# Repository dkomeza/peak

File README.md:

# peak
A small e-bike display meant for VESC

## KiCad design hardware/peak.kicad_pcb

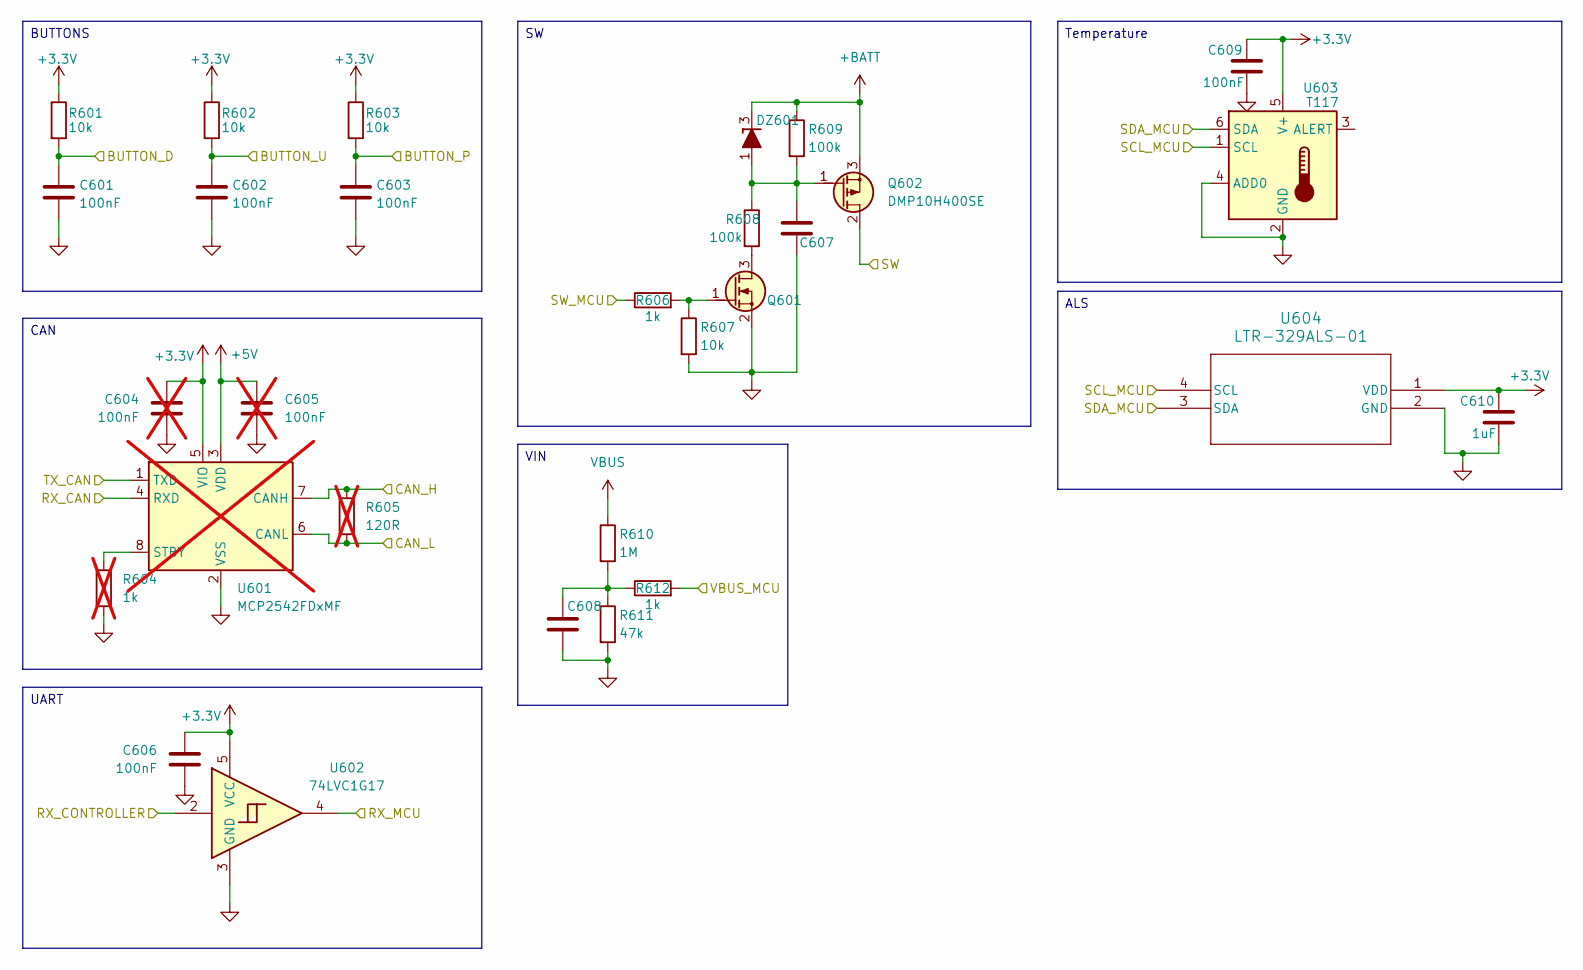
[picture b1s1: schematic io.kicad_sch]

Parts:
C601, C602, C603, C606, C609: 100nF; C_0603_1608Metric
C604, C605: 100nF; C_0603_1608Metric; not fitted
C607: 100nF/100V; C_0805_2012Metric
C608, C610: 1uF; C_0603_1608Metric
DZ601: BZX84-C12; SOT-23
Q601: BSS123; SOT-23
Q602: DMP10H400SE; SOT-223-3_TabPin2
R601, R602, R603, R607: 10k; R_0603_1608Metric
R604: 1k; R_0603_1608Metric; not fitted
R605: 120R; R_0603_1608Metric; not fitted
R606, R612: 1k; R_0603_1608Metric
R608, R609: 100k; R_0805_2012Metric
R610: 1M; R_0603_1608Metric
R611: 47k; R_0603_1608Metric
U601: MCP2542FDxMF; DFN-8-1EP_3x3mm_P0.65mm_EP1.55x2.4mm; not fitted
U602: 74LVC1G17; SOT-23-5
U603: T117; DFN-6-1EP_2x2mm_P0.65mm_EP1x1.6mm
U604: LTR-329ALS-01; LTR-329ALS-01_LTO

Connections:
+3.3V: C604.1, C606.1, C609.1, C610.1, R601.1, R602.1, R603.1, U601.5 (VIO), U602.5 (VCC), U603.5 (V+), U604.1 (VDD); also elsewhere on the board
+5V: C605.1, U601.3 (VDD); also elsewhere on the board
+BATT: DZ601.3 (K), Q602.3 (S), R609.1; also elsewhere on the board
/Connection/Button_D: C601.1, R601.2; also elsewhere on the board
/Connection/Button_P: C603.1, R603.2; also elsewhere on the board
/Connection/Button_U: C602.1, R602.2; also elsewhere on the board
/Connection/CANH: R605.1, U601.7 (CANH); also elsewhere on the board
/Connection/CANL: R605.2, U601.6 (CANL); also elsewhere on the board
/Connection/RX: U602.2; also elsewhere on the board
/Connection/SW: Q602.2 (D); also elsewhere on the board
/IO/SCL_MCU: U603.1 (SCL), U604.4 (SCL); also elsewhere on the board
/IO/SDA_MCU: U603.6 (SDA), U604.3 (SDA); also elsewhere on the board
/IO/SW_MCU: R606.1; also elsewhere on the board
/IO/VBUS_MCU: R612.2; also elsewhere on the board
/MCU/RX1: U601.4 (RXD), U602.4; also elsewhere on the board
/MCU/TX1: U601.1 (TXD); also elsewhere on the board
GND: C601.2, C602.2, C603.2, C604.2, C605.2, C606.2, C607.2, C608.2, C609.2, C610.2, Q601.2 (S), R604.2, R607.2, R611.2, U601.2 (VSS), U601.9 (VSS), U602.3 (GND), U603.2 (GND), U603.4 (ADD0), U604.2 (GND); also elsewhere on the board
unnamed: C608.1, R610.2, R611.1, R612.1
unnamed: C607.1, DZ601.1 (A), Q602.1 (G), R608.1, R609.2
unnamed: Q601.3 (D), R608.2
unnamed: Q601.1 (G), R606.2, R607.1
unnamed: R604.1, U601.8 (STBY)
VBUS: R610.1; also elsewhere on the board

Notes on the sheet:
Temperature
ALS
VIN
UART
BUTTONS
CAN

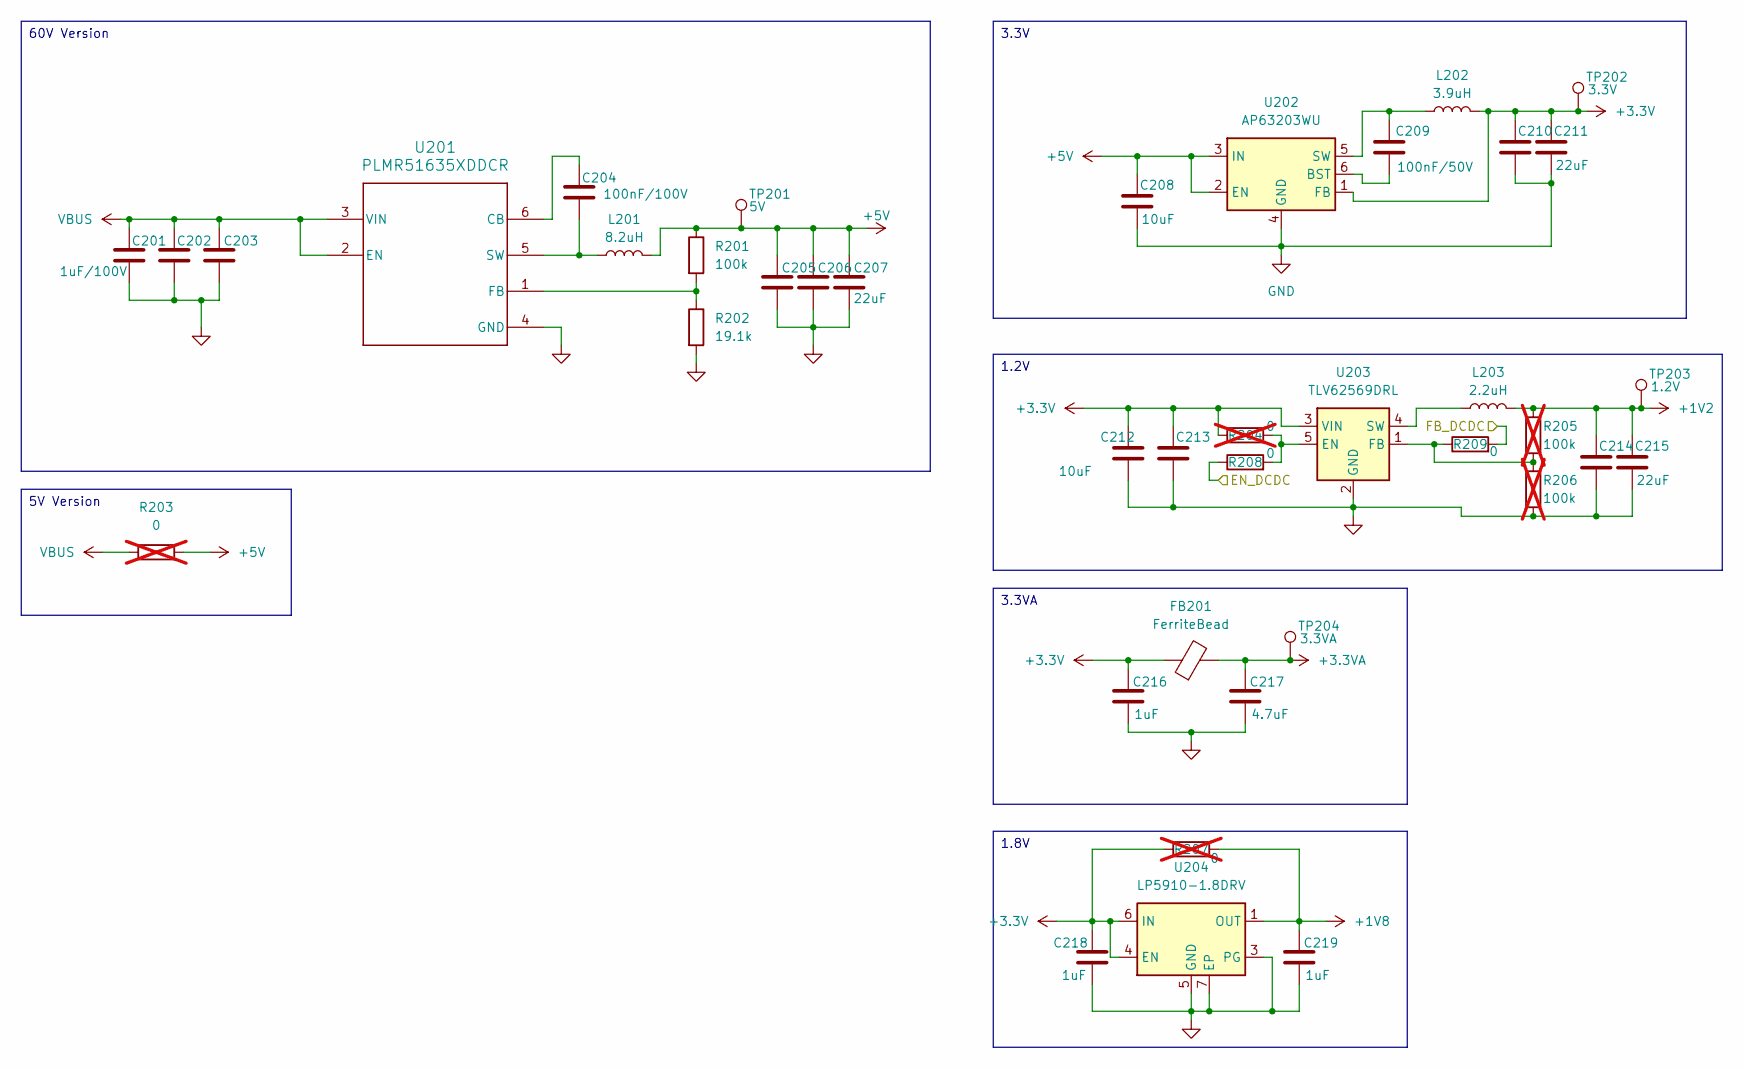
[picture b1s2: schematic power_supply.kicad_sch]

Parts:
C201, C202, C203: 1uF/100V; C_1206_3216Metric
C204: 100nF/100V; C_0805_2012Metric
C205, C206, C207, C210, C211, C214, C215: 22uF; C_0805_2012Metric
C208, C212: 10uF; C_0805_2012Metric
C209: 100nF/50V; C_0603_1608Metric
C213: 4.7nF; C_0603_1608Metric
C216, C218, C219: 1uF; C_0603_1608Metric
C217: 4.7uF; C_0603_1608Metric
FB201: FerriteBead; L_0805_2012Metric
L201: 8.2uH; L_Bourns_SRP5030T
L202: 3.9uH; L_APV_ANR4030
L203: 2.2uH; L_1008_2520Metric
R201: 100k; R_0603_1608Metric
R202: 19.1k; R_0603_1608Metric
R203: 0; R_0603_1608Metric; not fitted
R204, R207: 0; R_0402_1005Metric; not fitted
R205, R206: 100k; R_0402_1005Metric; not fitted
R208, R209: 0; R_0402_1005Metric
TP201: 5V; TestPoint_Pad_D1.0mm
TP202: 3.3V; TestPoint_Pad_D1.0mm
TP203: 1.2V; TestPoint_Pad_D1.0mm
TP204: 3.3VA; TestPoint_Pad_D1.0mm
U201: PLMR51635XDDCR; SOT-23-6
U202: AP63203WU; TSOT-23-6
U203: TLV62569DRL; SOT-563
U204: LP5910-1.8DRV; WSON-6-1EP_2x2mm_P0.65mm_EP1x1.6mm

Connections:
+1V2: C214.1, C215.1, L203.2, R205.1, TP203.1; also elsewhere on the board
+1V8: C219.1, R207.2, U204.1 (OUT); also elsewhere on the board
+3.3V: C210.1, C211.1, C212.1, C213.1, C216.1, C218.1, FB201.1, L202.2, R204.1, R207.1, TP202.1, U202.1 (FB), U203.3 (VIN), U204.4 (EN), U204.6 (IN); also elsewhere on the board
+3.3VA: C217.1, FB201.2, TP204.1; also elsewhere on the board
+5V: C205.1, C206.1, C207.1, C208.1, L201.2, R201.1, R203.2, TP201.1, U202.2 (EN), U202.3 (IN); also elsewhere on the board
/MCU/EN_DCDC: R208.1; also elsewhere on the board
/MCU/FB_DCDC: R209.2; also elsewhere on the board
GND: C201.2, C202.2, C203.2, C205.2, C206.2, C207.2, C208.2, C210.2, C211.2, C212.2, C213.2, C214.2, C215.2, C216.2, C217.2, C218.2, C219.2, R202.2, R206.2, U201.4 (GND), U202.4 (GND), U203.2 (GND), U204.3 (PG), U204.5 (GND), U204.7 (EP); also elsewhere on the board
unnamed: C204.1, U201.6 (CB)
unnamed: R201.2, R202.1, U201.1 (FB)
unnamed: C204.2, L201.1, U201.5 (SW)
unnamed: C209.2, U202.6 (BST)
unnamed: C209.1, L202.1, U202.5 (SW)
unnamed: R204.2, R208.2, U203.5 (EN)
unnamed: R205.2, R206.1, R209.1, U203.1 (FB)
unnamed: L203.1, U203.4 (SW)
VBUS: C201.1, C202.1, C203.1, R203.1, U201.2 (EN), U201.3 (VIN); also elsewhere on the board

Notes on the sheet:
3.3VA
3.3V
5V Version
60V Version
1.8V
1.2V

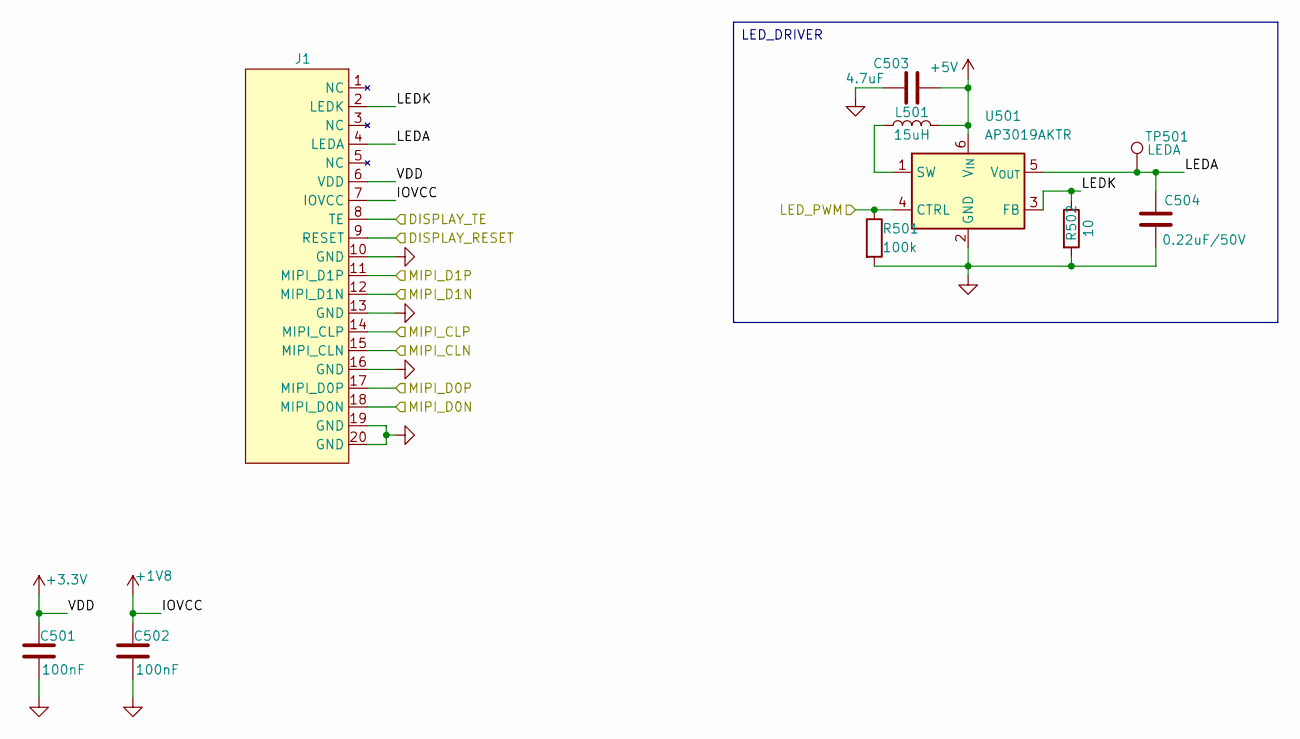
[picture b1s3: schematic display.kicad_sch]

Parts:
C501, C502: 100nF; C_0402_1005Metric
C503: 4.7uF; C_0603_1608Metric
C504: 0.22uF/50V; C_0805_2012Metric
J1: 5034802000
L501: 15uH; L_1210_3225Metric
R501: 100k; R_0603_1608Metric
R502: 10; R_0805_2012Metric
TP501: LEDA; TestPoint_Pad_D1.0mm
U501: AP3019AKTR; SOT-23-6

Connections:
+1V8: C502.1, J1.7 (IOVCC); also elsewhere on the board
+3.3V: C501.1, J1.6 (VDD); also elsewhere on the board
+5V: C503.2, L501.2, U501.6 (V_{IN}); also elsewhere on the board
/Display/DISPLAY_RESET: J1.9 (RESET); also elsewhere on the board
/Display/DISPLAY_TE: J1.8 (TE); also elsewhere on the board
/Display/LEDA: C504.1, J1.4 (LEDA), TP501.1, U501.5 (V_{OUT})
/Display/LEDK: J1.2 (LEDK), R502.1, U501.3 (FB)
/Display/LED_PWM: R501.1, U501.4 (CTRL); also elsewhere on the board
/Display/MIPI_CLN: J1.15 (MIPI_CLN); also elsewhere on the board
/Display/MIPI_CLP: J1.14 (MIPI_CLP); also elsewhere on the board
/Display/MIPI_D0N: J1.18 (MIPI_D0N); also elsewhere on the board
/Display/MIPI_D0P: J1.17 (MIPI_D0P); also elsewhere on the board
/Display/MIPI_D1N: J1.12 (MIPI_D1N); also elsewhere on the board
/Display/MIPI_D1P: J1.11 (MIPI_D1P); also elsewhere on the board
GND: C501.2, C502.2, C503.1, C504.2, J1.10 (GND), J1.13 (GND), J1.16 (GND), J1.19 (GND), J1.20 (GND), R501.2, R502.2, U501.2 (GND); also elsewhere on the board
unnamed: L501.1, U501.1 (SW)

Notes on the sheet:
LED_DRIVER

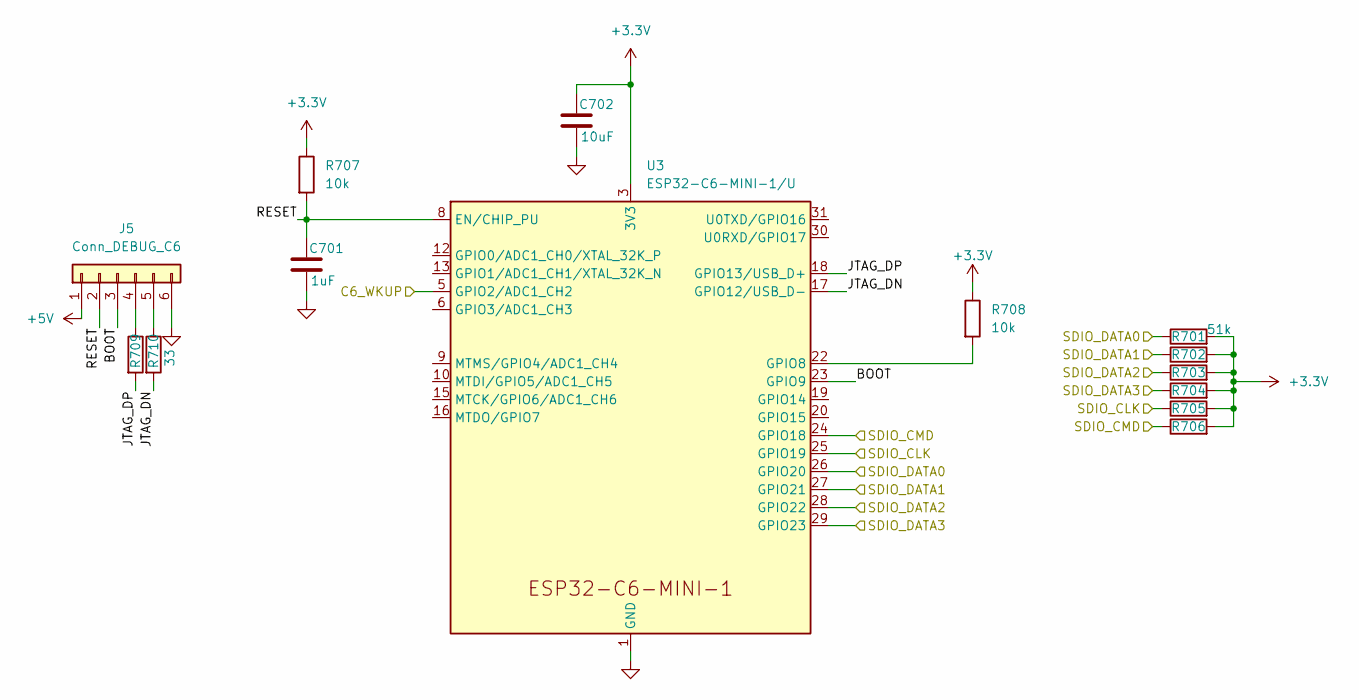
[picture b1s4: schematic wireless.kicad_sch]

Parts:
C701: 1uF; C_0603_1608Metric
C702: 10uF; C_0603_1608Metric
J5: Conn_DEBUG_C6; JST_SHL_SM06B-SHLS-TF_1x06-1MP_P1.00mm_Horizontal
R701, R702, R703, R704, R705, R706: 51k; R_0603_1608Metric
R707, R708: 10k; R_0603_1608Metric
R709, R710: 33; R_0402_1005Metric
U3: ESP32-C6-MINI-1/U; ESP32-C6-MINI-1

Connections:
+3.3V: C702.1, R701.2, R702.2, R703.2, R704.2, R705.2, R706.2, R707.1, R708.1, U3.3 (3V3); also elsewhere on the board
+5V: J5.1; also elsewhere on the board
/MCU/C6_WKUP: U3.5 (GPIO2/ADC1_CH2); also elsewhere on the board
/MCU/SDIO_CLK: R705.1, U3.25 (GPIO19); also elsewhere on the board
/MCU/SDIO_CMD: R706.1, U3.24 (GPIO18); also elsewhere on the board
/MCU/SDIO_DATA0: R701.1, U3.26 (GPIO20); also elsewhere on the board
/MCU/SDIO_DATA1: R702.1, U3.27 (GPIO21); also elsewhere on the board
/MCU/SDIO_DATA2: R703.1, U3.28 (GPIO22); also elsewhere on the board
/MCU/SDIO_DATA3: R704.1, U3.29 (GPIO23); also elsewhere on the board
/Wireless/BOOT: J5.3, U3.23 (GPIO9)
/Wireless/JTAG_DN: R710.2, U3.17 (GPIO12/USB_D-)
/Wireless/JTAG_DP: R709.2, U3.18 (GPIO13/USB_D+)
/Wireless/RESET: C701.1, J5.2, R707.2, U3.8 (EN/CHIP_PU)
GND: C701.2, C702.2, J5.6, U3.1 (GND), U3.2 (GND), U3.11 (GND), U3.14 (GND), U3.36 (GND), U3.37 (GND), U3.38 (GND), U3.39 (GND), U3.40 (GND), U3.41 (GND), U3.42 (GND), U3.43 (GND), U3.44 (GND), U3.45 (GND), U3.46 (GND), U3.47 (GND), U3.48 (GND), U3.49 (GND), U3.50 (GND), U3.51 (GND), U3.52 (GND), U3.53 (GND); also elsewhere on the board
unnamed: J5.4, R709.1
unnamed: J5.5, R710.1
unnamed: R708.2, U3.22 (GPIO8)

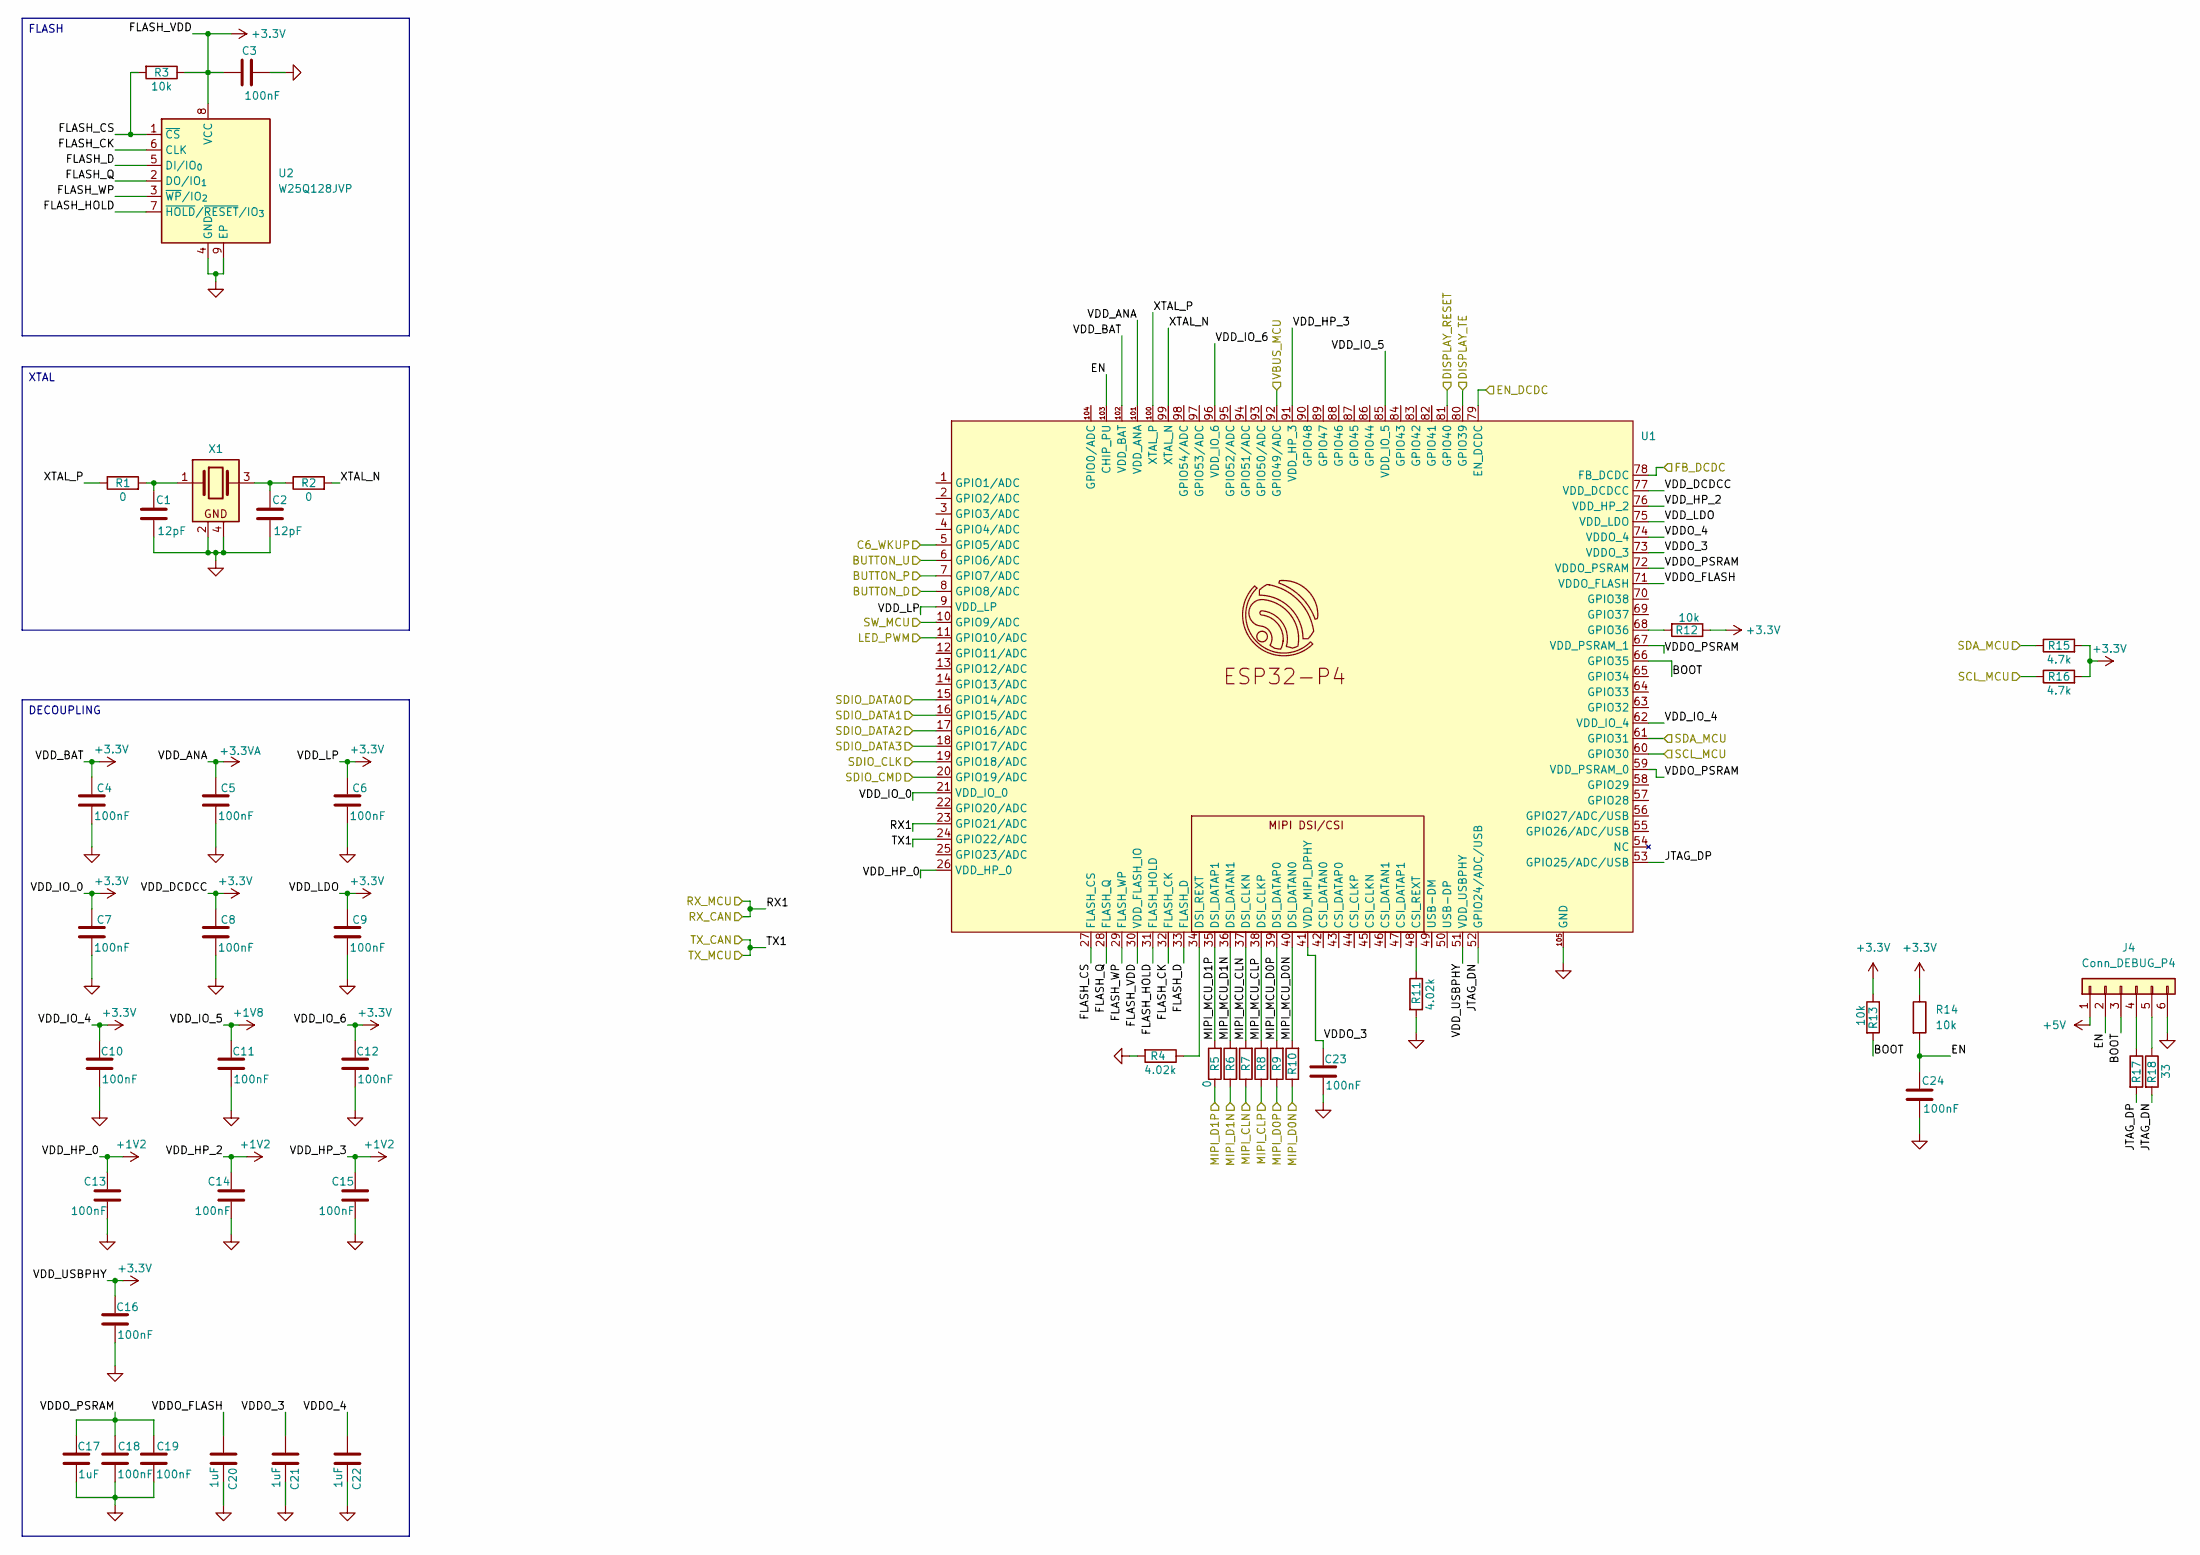
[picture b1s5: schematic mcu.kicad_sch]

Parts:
C1, C2: 12pF; C_0402_1005Metric
C3, C4, C5, C6, C7, C8, C9, C10, C11, C12, C13, C14, C15, C16, C18, C19, C23, C24: 100nF; C_0402_1005Metric
C17, C20, C21, C22: 1uF; C_0402_1005Metric
J4: Conn_DEBUG_P4; JST_SHL_SM06B-SHLS-TF_1x06-1MP_P1.00mm_Horizontal
R1, R2, R5, R6, R7, R8, R9, R10: 0; R_0402_1005Metric
R3, R12, R13, R14: 10k; R_0402_1005Metric
R4, R11: 4.02k; R_0402_1005Metric
R15, R16: 4.7k; R_0402_1005Metric
R17, R18: 33; R_0402_1005Metric
U1: ESP32-P4
U2: W25Q128JVP; WSON-8-1EP_6x5mm_P1.27mm_EP3.4x4.3mm
X1: ECS-400-10-37B2-CKY-TR; Crystal_SMD_2016-4Pin_2.0x1.6mm

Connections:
+1V2: C13.1, C14.1, C15.1, U1.26 (VDD_HP_0), U1.76 (VDD_HP_2), U1.91 (VDD_HP_3); also elsewhere on the board
+1V8: C11.1, U1.85 (VDD_IO_5); also elsewhere on the board
+3.3V: C3.1, C4.1, C6.1, C7.1, C8.1, C9.1, C10.1, C12.1, C16.1, R3.1, R12.1, R13.1, R14.1, R15.2, R16.2, U1.9 (VDD_LP), U1.21 (VDD_IO_0), U1.30 (VDD_FLASH_IO), U1.51 (VDD_USBPHY), U1.62 (VDD_IO_4), U1.75 (VDD_LDO), U1.77 (VDD_DCDCC), U1.96 (VDD_IO_6), U1.102 (VDD_BAT), U2.8 (VCC); also elsewhere on the board
+3.3VA: C5.1, U1.101 (VDD_ANA); also elsewhere on the board
+5V: J4.1; also elsewhere on the board
/Connection/Button_D: U1.8 (GPIO8/ADC); also elsewhere on the board
/Connection/Button_P: U1.7 (GPIO7/ADC); also elsewhere on the board
/Connection/Button_U: U1.6 (GPIO6/ADC); also elsewhere on the board
/Display/DISPLAY_RESET: U1.81 (GPIO40); also elsewhere on the board
/Display/DISPLAY_TE: U1.80 (GPIO39); also elsewhere on the board
/Display/LED_PWM: U1.11 (GPIO10/ADC); also elsewhere on the board
/Display/MIPI_CLN: R7.1; also elsewhere on the board
/Display/MIPI_CLP: R8.1; also elsewhere on the board
/Display/MIPI_D0N: R10.1; also elsewhere on the board
/Display/MIPI_D0P: R9.1; also elsewhere on the board
/Display/MIPI_D1N: R6.1; also elsewhere on the board
/Display/MIPI_D1P: R5.1; also elsewhere on the board
/IO/SCL_MCU: R16.1, U1.60 (GPIO30); also elsewhere on the board
/IO/SDA_MCU: R15.1, U1.61 (GPIO31); also elsewhere on the board
/IO/SW_MCU: U1.10 (GPIO9/ADC); also elsewhere on the board
/IO/VBUS_MCU: U1.92 (GPIO49/ADC); also elsewhere on the board
/MCU/BOOT: J4.3, R13.2, U1.66 (GPIO35)
/MCU/C6_WKUP: U1.5 (GPIO5/ADC); also elsewhere on the board
/MCU/EN: C24.1, J4.2, R14.2, U1.103 (CHIP_PU)
/MCU/EN_DCDC: U1.79 (EN_DCDC); also elsewhere on the board
/MCU/FB_DCDC: U1.78 (FB_DCDC); also elsewhere on the board
/MCU/FLASH_CK: U1.32 (FLASH_CK), U2.6 (CLK)
/MCU/FLASH_CS: R3.2, U1.27 (FLASH_CS), U2.1 (~CS)
/MCU/FLASH_D: U1.33 (FLASH_D), U2.5 (DI/IO_{0})
/MCU/FLASH_HOLD: U1.31 (FLASH_HOLD), U2.7 (~HOLD/~RESET/IO_{3})
/MCU/FLASH_Q: U1.28 (FLASH_Q), U2.2 (DO/IO_{1})
/MCU/FLASH_WP: U1.29 (FLASH_WP), U2.3 (~WP/IO_{2})
/MCU/JTAG_DN: R18.2, U1.52 (GPIO24/ADC/USB)
/MCU/JTAG_DP: R17.2, U1.53 (GPIO25/ADC/USB)
/MCU/MIPI_MCU_CLN: R7.2, U1.37 (DSI_CLKN)
/MCU/MIPI_MCU_CLP: R8.2, U1.38 (DSI_CLKP)
/MCU/MIPI_MCU_D0N: R10.2, U1.40 (DSI_DATAN0)
/MCU/MIPI_MCU_D0P: R9.2, U1.39 (DSI_DATAP0)
/MCU/MIPI_MCU_D1N: R6.2, U1.36 (DSI_DATAN1)
/MCU/MIPI_MCU_D1P: R5.2, U1.35 (DSI_DATAP1)
/MCU/RX1: U1.23 (GPIO21/ADC); also elsewhere on the board
/MCU/SDIO_CLK: U1.19 (GPIO18/ADC); also elsewhere on the board
/MCU/SDIO_CMD: U1.20 (GPIO19/ADC); also elsewhere on the board
/MCU/SDIO_DATA0: U1.15 (GPIO14/ADC); also elsewhere on the board
/MCU/SDIO_DATA1: U1.16 (GPIO15/ADC); also elsewhere on the board
/MCU/SDIO_DATA2: U1.17 (GPIO16/ADC); also elsewhere on the board
/MCU/SDIO_DATA3: U1.18 (GPIO17/ADC); also elsewhere on the board
/MCU/TX1: U1.24 (GPIO22/ADC); also elsewhere on the board
/MCU/VDDO_3: C21.1, C23.1, U1.41 (VDD_MIPI_DPHY), U1.73 (VDDO_3)
/MCU/VDDO_4: C22.1, U1.74 (VDDO_4)
/MCU/VDDO_FLASH: C20.1, U1.71 (VDDO_FLASH)
/MCU/VDDO_PSRAM: C17.1, C18.1, C19.1, U1.59 (VDD_PSRAM_0), U1.67 (VDD_PSRAM_1), U1.72 (VDDO_PSRAM)
/MCU/XTAL_N: R2.2, U1.99 (XTAL_N)
/MCU/XTAL_P: R1.1, U1.100 (XTAL_P)
GND: C1.2, C2.2, C3.2, C4.2, C5.2, C6.2, C7.2, C8.2, C9.2, C10.2, C11.2, C12.2, C13.2, C14.2, C15.2, C16.2, C17.2, C18.2, C19.2, C20.2, C21.2, C22.2, C23.2, C24.2, J4.6, R4.2, R11.2, U1.105 (GND), U2.4 (GND), U2.9 (EP), X1.2, X1.4; also elsewhere on the board
unnamed: C1.1, R1.2, X1.1
unnamed: C2.1, R2.1, X1.3
unnamed: J4.4, R17.1
unnamed: J4.5, R18.1
unnamed: R11.1, U1.48 (CSI_REXT)
unnamed: R4.1, U1.34 (DSI_REXT)
unnamed: R12.2, U1.68 (GPIO36)

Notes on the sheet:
XTAL
FLASH
DECOUPLING

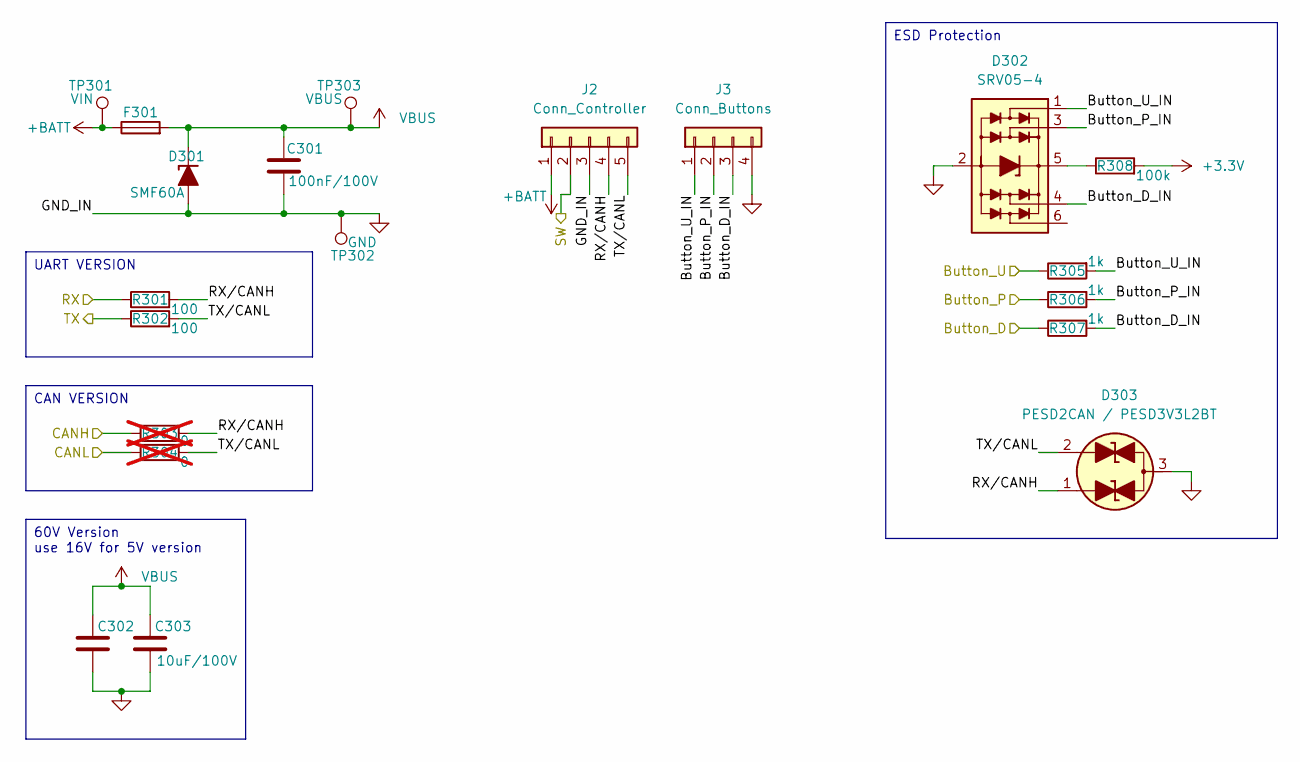
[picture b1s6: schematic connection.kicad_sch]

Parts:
C301: 100nF/100V; C_0805_2012Metric
C302, C303: 10uF/100V; C_1206_3216Metric
D301: SMF60A; D_SOD-123F
D302: SRV05-4; SOT-23-6
D303: PESD2CAN / PESD3V3L2BT; SOT-23
F301: Fuse; Fuse_1206_3216Metric
J2: Conn_Controller; Molex_PicoBlade_53261-0571_1x05-1MP_P1.25mm_Horizontal
J3: Conn_Buttons; Molex_PicoBlade_53261-0471_1x04-1MP_P1.25mm_Horizontal
R301, R302: 100; R_0603_1608Metric
R303, R304: 0; R_0603_1608Metric; not fitted
R305, R306, R307: 1k; R_0603_1608Metric
R308: 100k; R_0603_1608Metric
TP301: VIN; TestPoint_Pad_D1.0mm
TP302: GND; TestPoint_Pad_D1.0mm
TP303: VBUS; TestPoint_Pad_D1.0mm

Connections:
+3.3V: R308.2; also elsewhere on the board
+BATT: F301.1, J2.1, TP301.1; also elsewhere on the board
/Connection/Button_D: R307.1; also elsewhere on the board
/Connection/Button_D_IN: D302.4 (L3), J3.3, R307.2
/Connection/Button_P: R306.1; also elsewhere on the board
/Connection/Button_P_IN: D302.3 (L2), J3.2, R306.2
/Connection/Button_U: R305.1; also elsewhere on the board
/Connection/Button_U_IN: D302.1 (L1), J3.1, R305.2
/Connection/CANH: R303.1; also elsewhere on the board
/Connection/CANL: R304.1; also elsewhere on the board
/Connection/RX: R301.1; also elsewhere on the board
/Connection/RX/CANH: D303.1 (A1), J2.4, R301.2, R303.2
/Connection/SW: J2.2; also elsewhere on the board
/Connection/TX/CANL: D303.2 (A2), J2.5, R302.2, R304.2
/MCU/TX1: R302.1; also elsewhere on the board
GND: C301.2, C302.2, C303.2, D301.2 (A), D302.2 (VN), D303.3 (Com), J2.3, J3.4, TP302.1; also elsewhere on the board
unnamed: D302.5 (VP), R308.1
VBUS: C301.1, C302.1, C303.1, D301.1 (K), F301.2, TP303.1; also elsewhere on the board

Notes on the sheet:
CAN VERSION
ESD Protection
60V Version use 16V for 5V version
UART VERSION

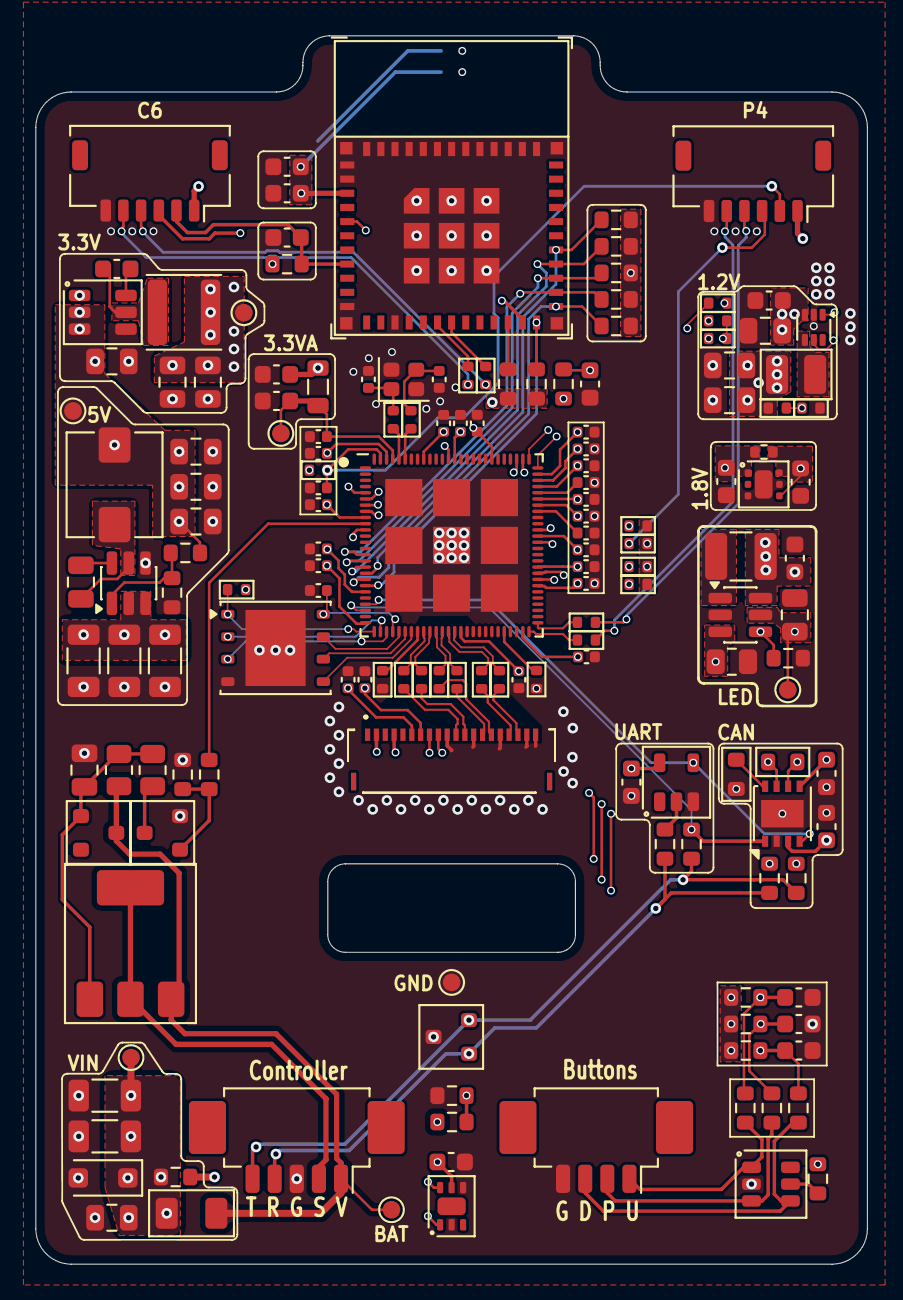
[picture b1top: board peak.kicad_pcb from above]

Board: 6 copper layers, 47.0 x 69.4 mm, 158 parts (1 on the bottom side), 97 nets.

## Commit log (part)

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2025-03-29 🔧 Add .gitignore
2025-03-29 ✨ Add hardware files
2025-03-29 📚 Fix typo
2025-04-22 ✨ Add initial software package
2025-06-22 ✨ Initial software update
2025-06-22 🐛 Fix submodules
2025-06-24 ✨ Add BLE serial
2025-06-28 ✨ VESC interface updates
2025-06-28 🐛 Separate VESC related functions into separate tasks, add RX and TX queue
2025-06-28 🔧 Try to debug firmware update
2025-11-09 ✨ Add schematic parts
2025-11-10 ✨ Further power supply schematic
2025-11-10 ✨ Add pulldown to disable the led by default
2025-11-13 ✨ Further schematic updates
2025-11-14 ✨ MCU updates
2025-12-02 📂 PCB updates
2025-12-08 🐛 Fix errors from rev1.0
2025-12-08 ✨ Finish rev 1.1
2026-01-10 🔨 Update the pcb
2026-01-13 🔥 Redo the PCB
2026-01-26 ✨ Final PCB updates
2026-03-02 ✨ Final PCB v.1 updates
2026-03-31 ✨ Update the bom
2026-04-02 🔥 Use new PCB
2026-04-02 🔥 Remove old dependencies
2026-04-02 ✨ Add T117 support
2026-04-04 ✨ Make buttons work
2026-04-15 Use LVGL editor
2026-04-27 ✨ Add boot mode selection
2026-04-27 🔨 Add deep_sleep placeholder
2026-04-27 🐛 Resume buttons after finishing mountain mode check
2026-04-27 Implement boot sequence (#1)
2026-04-27 🔥 Cleanup
2026-04-28 ✨ Add mountain mode callback to the boot sequence
2026-04-28 ✨ Add mountain mode callback to the boot sequence (#2)
2026-05-02 docs: add VESC UDP bridge rewrite spec
    Document the approved full rewrite design for the VESC bridge. The spec fixes UDP port 65102, preserves VESC packet framing, defines the one-client UDP peer model, and records that tests are out of s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
2026-05-02 ✨ Make VESC UDP-CAN bridge work
2026-05-03 ✨ Add BLE bridge
2026-05-03 🔨 Split the code into separate components
2026-05-05 ✨ Add input voltage sensing
2026-05-08 🐛 Fix BLE
2026-05-09 ✨ Add basic UART support
2026-05-09 ✨ Soft AP support
2026-05-09 ✨ OTA support
2026-05-11 ✨ Create get kt data function
2026-05-11 ✨ Complete kt protocol
2026-05-11 🐛 Fix errors
2026-05-12 ✨ Add peak esc support
2026-05-12 docs: add ride dashboard design
    Document the approved MVP direction for the Peak ride dashboard UI. The spec defines the display runtime, UI layer, dashboard data contract, mock-data scope, visual hierarchy, and verification approa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
2026-05-12 docs: add ride dashboard plan
    Document the task-by-task implementation plan for the LVGL ride dashboard MVP. The plan records the display runtime split, UI module structure, mock data path, build checkpoints, and verification ste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
2026-05-12 feat: add LVGL display runtime
    Compile the existing ST7701 display experiment as a proper display runtime. Register LVGL through the component manager, add UI module stubs, allocate draw buffers, register flush callbacks, initiali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
2026-05-12 fix: align IDF component constraint
    Lower the project IDF dependency constraint to match the configured IDF 5.5.1 toolchain. Adding LVGL forces component resolution, so the previous >=6.0.1 constraint prevented dependency solving befor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
2026-05-12 fix: add ST7701 panel dependency
    Register the external Espressif ST7701 panel driver required by the display runtime. The display source was newly added to the build and depends on esp_lcd_st7701.h, so the component and lockfile nee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
2026-05-12 fix: propagate display init errors
    Return recoverable display bring-up failures through esp_err_t instead of panicking during panel and callback setup.
    Handle failed panel draw requests by logging the error and releasing LVGL's flush state so rendering cannot wedge permanently.
2026-05-12 feat: add dashboard style tokens
    Centralize the dark dashboard colors and LVGL object styling helpers. These tokens keep the MVP screen visually consistent and leave room for richer gauge and font work later.
2026-05-12 fix: preserve dashboard widget layout
    Keep card and pill style helpers from clearing existing object styles so callers can size, align, or configure layout before applying shared visual tokens.
2026-05-13 fix: add Peak home parser stub
    Define the missing Peak home-main parser registered during ESC initialization. The stub mirrors the existing home-secondary parser shape so the component builds while real Peak data parsing remains f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
2026-05-13 feat: add ride dashboard screen
    Create the MVP LVGL dashboard hierarchy with status, battery, speed, power, segment, range, thermal, distance, time, and average speed widgets. The dashboard updates from a display-ready data model a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
2026-05-13 feat: add dashboard mock data
    Initialize the LVGL dashboard screen from the UI layer and refresh it with mock ride data on an LVGL timer. This keeps MVP rendering independent from ESC and sensor integration.
2026-05-13 fix: handle dashboard allocation failures
    Check required LVGL widget allocations while building the ride dashboard and propagate ESP_ERR_NO_MEM when construction cannot complete. Clean partial dashboard children and guard updates against inc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
2026-05-13 feat: start ride dashboard UI
    Initialize the display runtime during app startup so the LVGL ride dashboard boots with the firmware. The dashboard still uses mock data and does not depend on live ESC wiring.
2026-05-13 chore: expand OTA partitions
    Switch the firmware to a custom 16MB flash partition table with two 7.5MB OTA slots. This gives the current image substantial growth room while preserving OTA support and leaving a data partition at 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
2026-05-13 🔥 Remove unused docs
2026-05-13 ⬆️ Upgrade esp-idf
2026-05-14 Bug fixes
2026-05-23 docs: add loom graphics design
    Document the planned loom immediate-mode graphics component for the ESP32-P4 display stack.
    The design covers tiled RGB888 rendering, command recording, partial-buffer ownership, ESP32-P4 accelerator usage, text/font handling, and initial validation expectations. It keeps the existing displ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
2026-05-23 docs: add loom implementation plan
    Document the task-by-task implementation path for the loom graphics component.
    The plan covers the component API, command recording, RGB888 tiled rasterization, ESP LCD flushing, display integration, and final verification so implementation can proceed in small reviewed steps.
2026-05-23 feat: add loom public API
    Add the initial loom ESP-IDF component declaration and public headers for display, bitmap, font, and drawing APIs. This establishes the public type and function surface needed by later loom graphics 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
2026-05-23 fix: correct loom public API
    Expose esp_lcd as a public component dependency because the loom public types include esp_lcd_panel_handle_t. Also use positional aggregate initialization in public inline helpers so the headers rema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
2026-05-23 feat: add loom command lifecycle
    Implement the Loom private state, display lifecycle, command recording, clipping, dirty invalidation, and geometry bounds helpers. The new lifecycle allocates command and tile buffers with the reques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
2026-05-23 fix: allow clipped loom commands
    Record valid Loom commands even when their bounds are fully outside the active clip or screen. Empty clipped bounds no longer set the frame sticky error; only visible bounds update the dirty region, 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
2026-05-23 fix: harden loom command recording
    Add 8-bit heap capabilities to Loom allocations and guard tile size calculations against overflow. Harden command bounds math with int64_t-based saturation, validate bitmap formats and strides, and c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
2026-05-23 fix: correct loom tile offsets
    Use absolute screen columns when addressing RGB888 pixels inside the full-width tile stride, while keeping rows relative to the visible tile y origin. Also start per-row tile clears at tile_rect.x so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
2026-05-23 fix: clip loom line rasterization
    Clip line segments to the visible command rect expanded by the square brush before running Bresenham. This prevents huge offscreen endpoints from causing signed overflow or excessive iteration, and m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
2026-05-23 fix: add loom ESP32-P4 flush
    Implement the ESP32-P4 loom backend flush entry point so rendered tiles are forwarded to the configured esp_lcd panel handle. The function validates the loom, tile buffer, panel handle, and tile rect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
2026-05-23 fix: flush full-width loom tiles
    Render and flush dirty frames as full-width vertical tiles so the ESP LCD backend receives tightly packed RGB888 rectangle data. The dirty region still bounds the vertical tile range, preserving part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
2026-05-23 fix: pack loom dirty tile rows
    Restore horizontal dirty-rectangle flushing while making raster tiles compact for the ESP LCD backend. Tile pixel addressing now uses tile-local x coordinates and a tile-width row stride, and row cle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
2026-05-23 fix: wait for loom DPI flushes
    Register the MIPI DPI color-transfer callback when loom is created and use a binary semaphore to wait for each DMA2D-backed bitmap transfer before reusing tile buffers. The semaphore is cleaned up wi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
    Also check the display initialization result in the main app task so display setup failures are surfaced through ESP_ERROR_CHECK.
2026-05-23 feat: draw display demo with loom
    Wire the loom renderer into the existing display initialization path and replace the direct pixel test with a tiled RGB888 smoke demo.
    The ESP32-P4 backend now documents DPI callback ownership and clears callbacks on destroy so DMA2D-backed panel transfers cannot outlive loom-owned tile buffers.
2026-05-23 feat: log loom frame timing
    Add debug timing around tiled loom frame rendering with command count and elapsed microseconds.
    The loom component now declares its private esp_timer dependency so timing diagnostics build independently of the app component.
2026-05-24 perf: optimize loom rendering
    Pipeline tile flushes across the two loom buffers so CPU rasterization can overlap with the LCD DMA transfer. Add faster RGB888 fill paths, PPA-backed solid fills, and generated font assets used by t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
2026-05-24 feat: wire display demo dependencies
    Use the ST7701 component dependency from the main manifest, record the resolved lockfile and sdkconfig updates, and run the loom display demo as a persistent task with text rendering. Update the host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
2026-05-24 docs: add agent guidance
    Document the repo scope, ESP32-P4 and ESP32-C6 ESP-Hosted hardware split, embedded firmware priorities, and the project preference for beneficial refactors. This gives future agents a clear operating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
2026-05-24 feat: add ESC controller commands
    Add a shared ESC controller interface and wire PEAK and KT implementations through it. Document the CycleIQ CAN protocol and add command helpers for power, gear, support mode, and ride mode handling.
2026-05-24 feat: wire controls into display UI
    Connect button events to ESC controller commands and display feedback. Add larger Loom font assets and render live PEAK telemetry values for speed, gear, support mode, battery, temperature, and power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
2026-05-24 🐛 Correct CAN ID naming
2026-05-26 refactor: use CycleIQ SDK for Peak ESC
    Add the CycleIQ protocol SDK as an ESP-IDF submodule and wire the ESC component to its public frame helpers. Peak ESC commands now build SDK frames before sending them over the existing CAN transport.
    Replace local protocol constants with SDK packet IDs, lengths, and version helpers while preserving the existing display telemetry snapshot. The obsolete in-repo protocol headers are removed so the S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
2026-05-31 feat: extract loom submodule
    Replace the in-tree loom component with the standalone loom repository and point the superproject at the new clean root commit.
    Update the Peak display path to create loom through the ESP-IDF adapter so the public loom API can stay platform-neutral while preserving the existing RGB888 tiled renderer and panel flush behavior.
2026-05-31 🔨 Move loom to separate repo
2026-05-31 chore: update submodules
2026-05-31 chore: update esp-hosted
2026-05-31 chore: remove codex docs
2026-06-07 ✨ Add loom benchmark
2026-06-28 fix: swap button pins for loom update
